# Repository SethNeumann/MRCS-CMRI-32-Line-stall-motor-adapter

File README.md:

# REPO NAME: MRCS-CMRI-32-Line-stall-motor-adapter
## License: Creative Commons Attribution-NonCommercial-ShareAlike

This board implements the "Driving Low Current Stall-Type Switch Motors" section 
on pages 7-8 - 7-10 of  Dr Chubb's 2010 CMRI Applications Handbook
First line: A short description of the project, used as a subtitle or tagline

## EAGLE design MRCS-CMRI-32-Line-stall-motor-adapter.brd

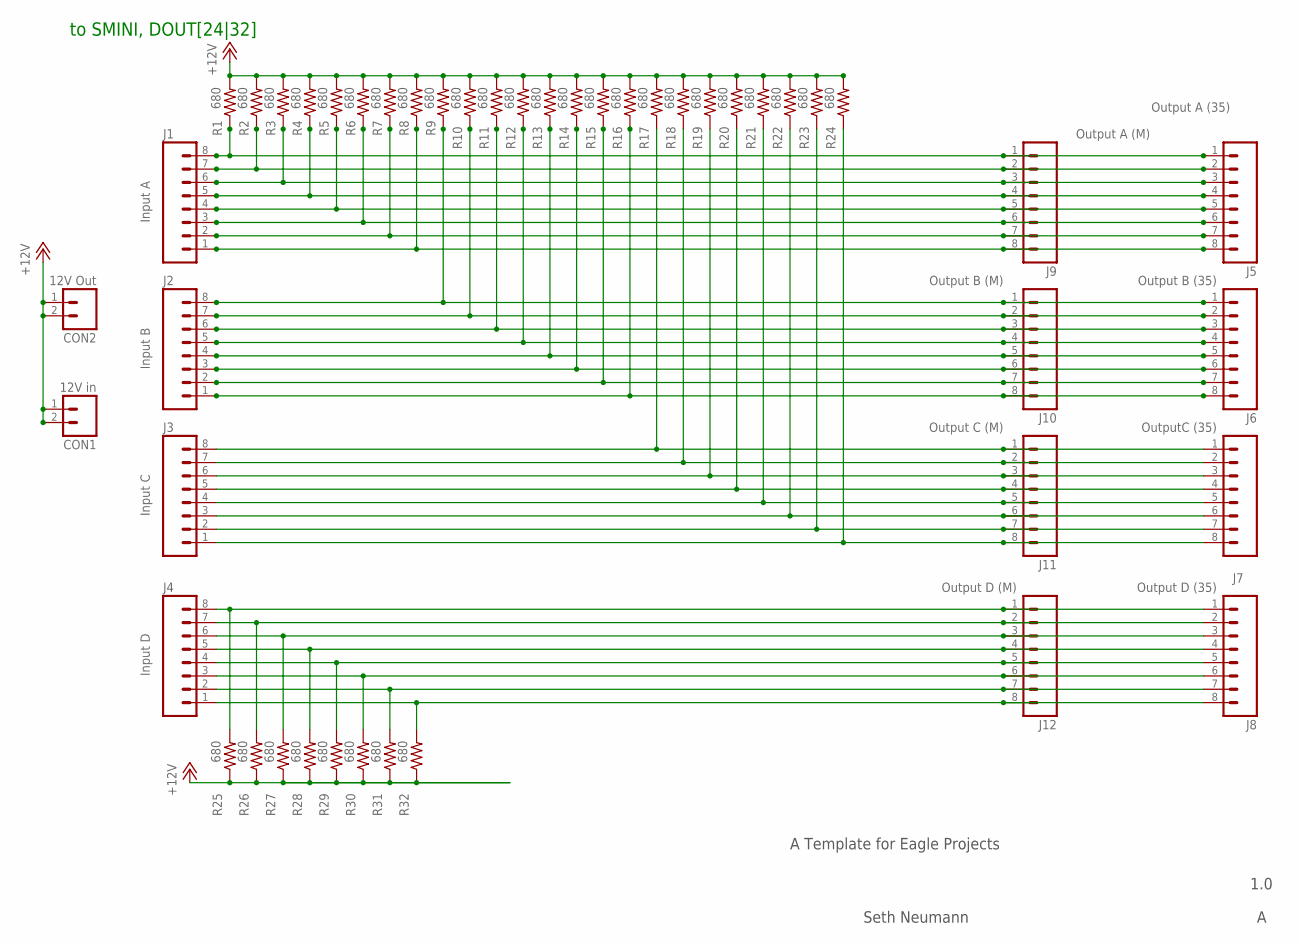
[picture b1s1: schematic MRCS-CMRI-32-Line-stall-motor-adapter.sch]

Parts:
CON1: 12V in; SCREWTERMINAL-5MM-2
CON2: 12V Out; SCREWTERMINAL-5MM-2
J1: Input A; KK-156-8-F
J2: Input B; KK-156-8-F
J3: Input C; KK-156-8-F
J4: Input D; KK-156-8-F
J5: Output A (35); SCREWTERMINAL-3.5MM-8
J6: Output B (35); SCREWTERMINAL-3.5MM-8
J7: OutputC (35); SCREWTERMINAL-3.5MM-8
J8: Output D (35); SCREWTERMINAL-3.5MM-8
J9: Output A (M); KK-156-8-F
J10: Output B (M); KK-156-8-F
J11: Output C (M); KK-156-8-F
J12: Output D (M); KK-156-8-F
R1, R2, R3, R4, R5, R6, R7, R8, R9, R10, R11, R12, R13, R14, R15, R16, R17, R18, R19, R20, R21, R22, R23, R24, R25, R26, R27, R28, R29, R30, R31, R32: 680; AXIAL-0.5

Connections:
+12V: CON1.1 (A), CON1.2 (B), CON2.1 (A), CON2.2 (B), R1.P$2 (2), R2.P$2 (2), R3.P$2 (2), R4.P$2 (2), R5.P$2 (2), R6.P$2 (2), R7.P$2 (2), R8.P$2 (2), R9.P$2 (2), R10.P$2 (2), R11.P$2 (2), R12.P$2 (2), R13.P$2 (2), R14.P$2 (2), R15.P$2 (2), R16.P$2 (2), R17.P$2 (2), R18.P$2 (2), R19.P$2 (2), R20.P$2 (2), R21.P$2 (2), R22.P$2 (2), R23.P$2 (2), R24.P$2 (2), R25.P$1 (1), R26.P$1 (1), R27.P$1 (1), R28.P$1 (1), R29.P$1 (1), R30.P$1 (1), R31.P$1 (1), R32.P$1 (1)
unnamed: J1.5, J5.4, J9.4, R4.P$1 (1)
unnamed: J1.8, J5.1, J9.1, R1.P$1 (1)
unnamed: J2.8, J6.1, J10.1, R9.P$1 (1)
unnamed: J1.7, J5.2, J9.2, R2.P$1 (1)
unnamed: J2.6, J6.3, J10.3, R11.P$1 (1)
unnamed: J3.8, J7.1, J11.1, R17.P$1 (1)
unnamed: J2.4, J6.5, J10.5, R13.P$1 (1)
unnamed: J2.3, J6.6, J10.6, R14.P$1 (1)
unnamed: J1.4, J5.5, J9.5, R5.P$1 (1)
unnamed: J1.3, J5.6, J9.6, R6.P$1 (1)
unnamed: J1.2, J5.7, J9.7, R7.P$1 (1)
unnamed: J1.1, J5.8, J9.8, R8.P$1 (1)
unnamed: J1.6, J5.3, J9.3, R3.P$1 (1)
unnamed: J2.7, J6.2, J10.2, R10.P$1 (1)
unnamed: J2.2, J6.7, J10.7, R15.P$1 (1)
unnamed: J2.1, J6.8, J10.8, R16.P$1 (1)
unnamed: J2.5, J6.4, J10.4, R12.P$1 (1)
unnamed: J3.7, J7.2, J11.2, R18.P$1 (1)
unnamed: J3.6, J7.3, J11.3, R19.P$1 (1)
unnamed: J3.5, J7.4, J11.4, R20.P$1 (1)
unnamed: J3.4, J7.5, J11.5, R21.P$1 (1)
unnamed: J3.3, J7.6, J11.6, R22.P$1 (1)
unnamed: J3.2, J7.7, J11.7, R23.P$1 (1)
unnamed: J3.1, J7.8, J11.8, R24.P$1 (1)
unnamed: J4.8, J8.1, J12.1, R25.P$2 (2)
unnamed: J4.7, J8.2, J12.2, R26.P$2 (2)
unnamed: J4.6, J8.3, J12.3, R27.P$2 (2)
unnamed: J4.5, J8.4, J12.4, R28.P$2 (2)
unnamed: J4.4, J8.5, J12.5, R29.P$2 (2)
unnamed: J4.3, J8.6, J12.6, R30.P$2 (2)
unnamed: J4.2, J8.7, J12.7, R31.P$2 (2)
unnamed: J4.1, J8.8, J12.8, R32.P$2 (2)

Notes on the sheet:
A Template for Eagle Projects
1.0
Seth Neumann
to SMINI, DOUT[24|32]

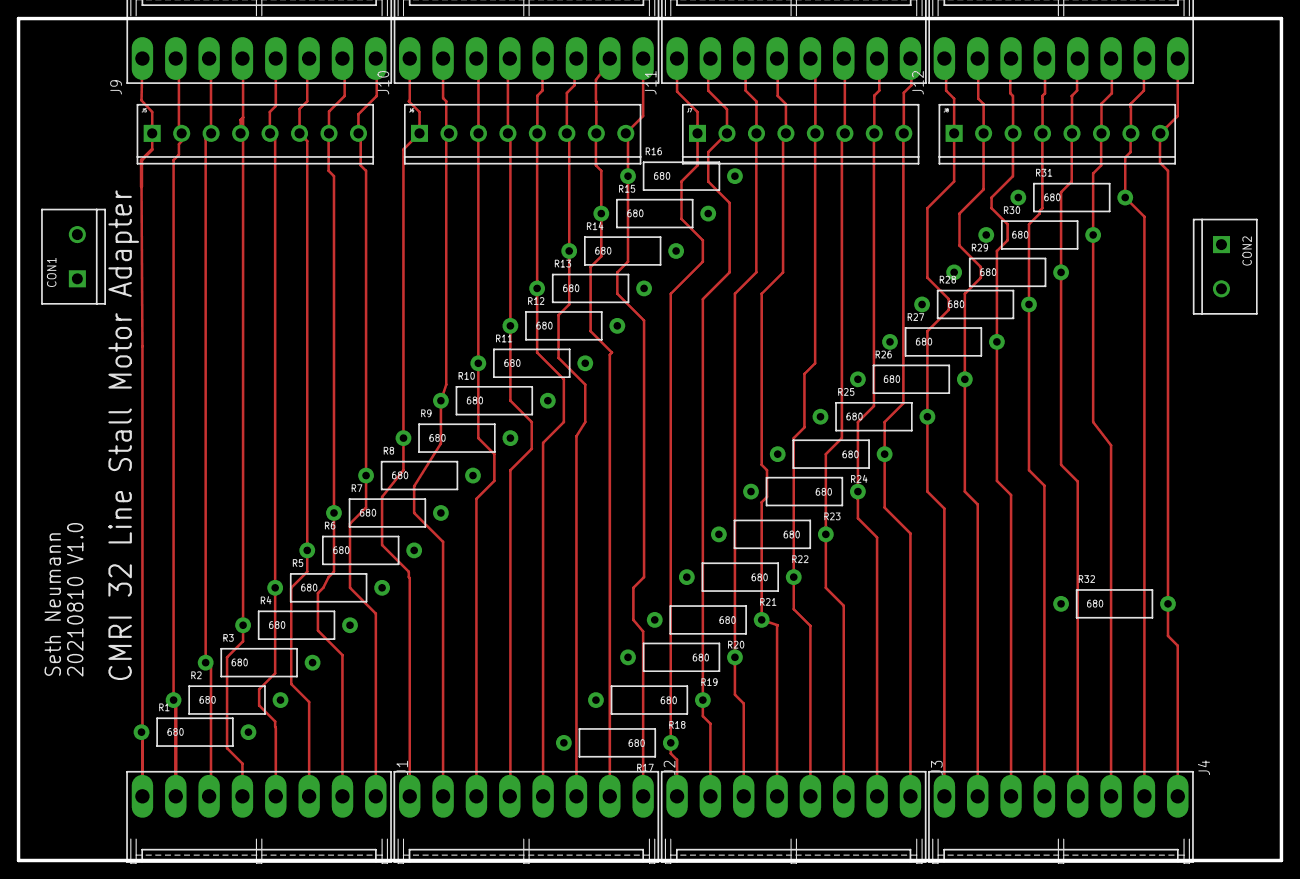
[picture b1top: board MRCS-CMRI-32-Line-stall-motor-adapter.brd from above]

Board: 2 copper layers, 150.0 x 100.0 mm, 49 parts (0 on the bottom side), 33 nets.

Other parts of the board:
U$1: MRCSLOGOTOP
U$2: MRCSLOGOBTM
U$3: CA-PROP65WARNING

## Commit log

2021-08-07 Initial Commit
    setting up the project
2021-08-07 initial commit
    setting the project up
2021-08-07 initial commit
    setting project up
2021-08-11 clean up at end of Version 1.0
    made pdfs of Schematic and layout, cleaned up work files. This version passes all electrical design rules and created a believable set of gerbers
2021-08-12 Moved 12V connectors out to front of board
    Mark Juett has made a bunch of these by hand and suggested that putting the 12V out front makes it easier to work with.

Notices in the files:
parts and their libraries:
SparkFun-Passives: Licensing: CC v3.0 Share-Alike You are welcome to use this library for commercial purposes.
